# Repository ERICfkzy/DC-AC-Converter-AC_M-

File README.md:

**DC-AC Converter PCB:**
Power supply unit for the simple transformer model
It converts the DC voltage (9v) to AC voltage at 50Hz to drive the transformer's primary. 
It is stepped up at the secondary based on the turns ratio of the transformer.
ATtiny85 chip generates PWM signals to switch ON/OFF the MOSFETs (2 N-channel).
Switching of the MOSFETs creates square waveform, hence converting DC to AC signals.
Same schematic diagram with two variants of PCB i.e. SMD-version1 and PTH-version2.

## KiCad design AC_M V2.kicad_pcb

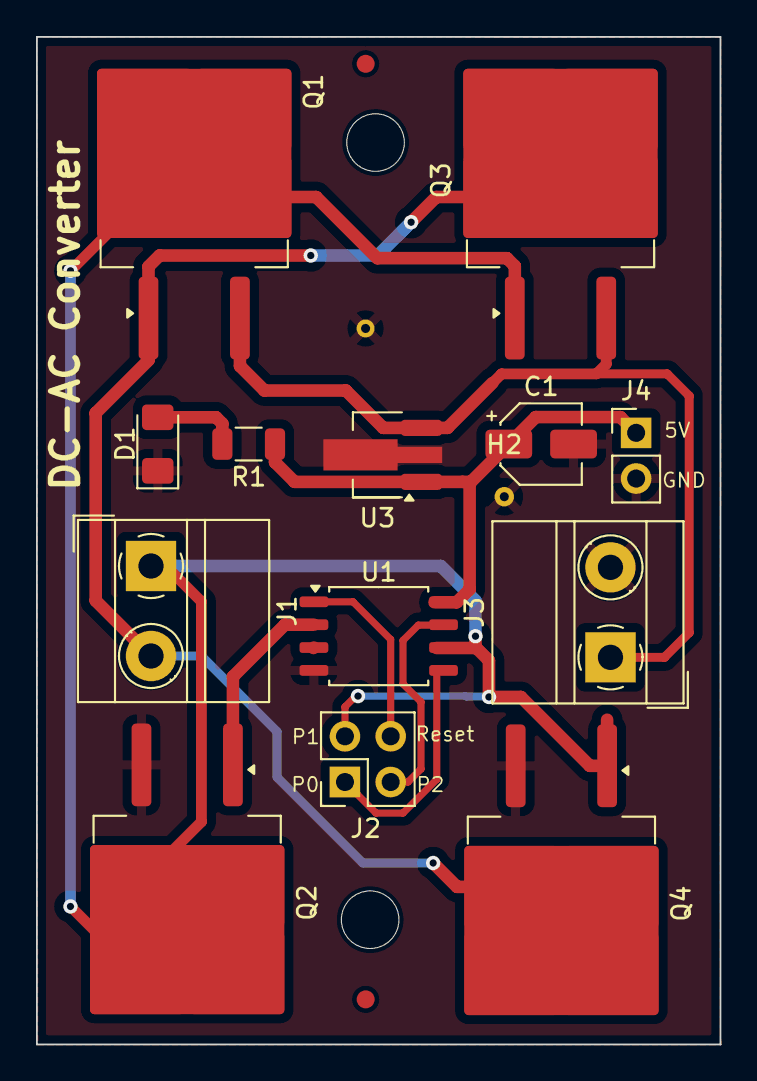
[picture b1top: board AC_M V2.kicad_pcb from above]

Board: 2 copper layers, 38.0 x 56.0 mm, 19 parts (0 on the bottom side), 10 nets.

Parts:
C1: C_Polarized_Small_US; CP_Elec_4x5.3
D1: LED; LED_1206_3216Metric_Pad1.42x1.75mm_HandSolder
FID1, FID2: Fiducial; Fiducial_0.5mm_Mask1mm
H1, H2: MountingHole_Pad; MountingHole_2.2mm_M2_DIN965_Pad
H3, H4: MountingHole; MountingHole_3.2mm_M3
J1, J3: Screw_Terminal_3.5mm_2; TerminalBlock_MetzConnect_Type011_RT05502HBWC_1x02_P5.00mm_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
J2: Conn_02x02_Counter_Clockwise; PinHeader_2x02_P2.54mm_Vertical
J4: Conn_01x02; PinHeader_1x02_P2.54mm_Vertical
Q1, Q3: IRF9540N; TO-263-2
Q2, Q4: IRFZ44NSTRLPBF; TO-263-2
R1: R; R_1206_3216Metric
U1: ATtiny85V-10P; SOP-8_5.28x5.23mm_P1.27mm
U3: L78L05_SOT89; SOT-89-3_Handsoldering

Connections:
/Reset: J2.4, U1.1 (~RESET/PB5)
/pin0: J2.1, U1.5 (AREF/PB0)
/pin2: J2.3, U1.7 (PB2)
GND: C1.2, D1.1 (K), H1.1, H2.1, J3.2, J4.2, Q2.3, Q4.3, U1.4 (GND), U3.2 (GND)
unnamed: D1.2 (A), R1.2
unnamed: J1.1, J2.2, Q1.2 (D), Q2.2, Q3.1 (G), Q4.1, U1.6 (PB1)
unnamed: J1.2, Q1.1 (G), Q3.2 (D), Q4.2
unnamed: J3.1, Q1.3 (S), Q3.3 (S), U3.3 (IN)
unnamed: C1.1, J4.1, R1.1, U1.8 (VCC), U3.1 (OUT)
unnamed: Q2.1, U1.2 (XTAL1/PB3)

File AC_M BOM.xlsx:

Designator | Footprint | Quantity | Value
C1 | CP_Elec_4x5.3 | 1 | C_Polarized_Small_US
D1 | 1206 | 1 | LED
J1, J3 | TerminalBlock_MetzConnect_Type011_RT05502HBWC_1x02_P5.00mm_Horizontal | 2 | Screw_Terminal_3.5mm_2
J2 | PinHeader_2x02_P2.54mm_Vertical | 1 | Conn_02x02_Counter_Clockwise
J4 | PinHeader_1x02_P2.54mm_Vertical | 1 | Conn_01x02
Q1, Q3 | TO-263-2 | 2 | IRF9540N
Q2, Q4 | TO-263-2 | 2 | IRFZ44NSTRLPBF
R1 | 1206 | 1 | R
U1 | SOP-8_5.28x5.23mm_P1.27mm | 1 | ATtiny85V-10P
U3 | SOT-89-3_Handsoldering | 1 | L78L05_SOT89

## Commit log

2025-04-24 first version PCB
2025-04-24 Create README.md
    Readme 1
